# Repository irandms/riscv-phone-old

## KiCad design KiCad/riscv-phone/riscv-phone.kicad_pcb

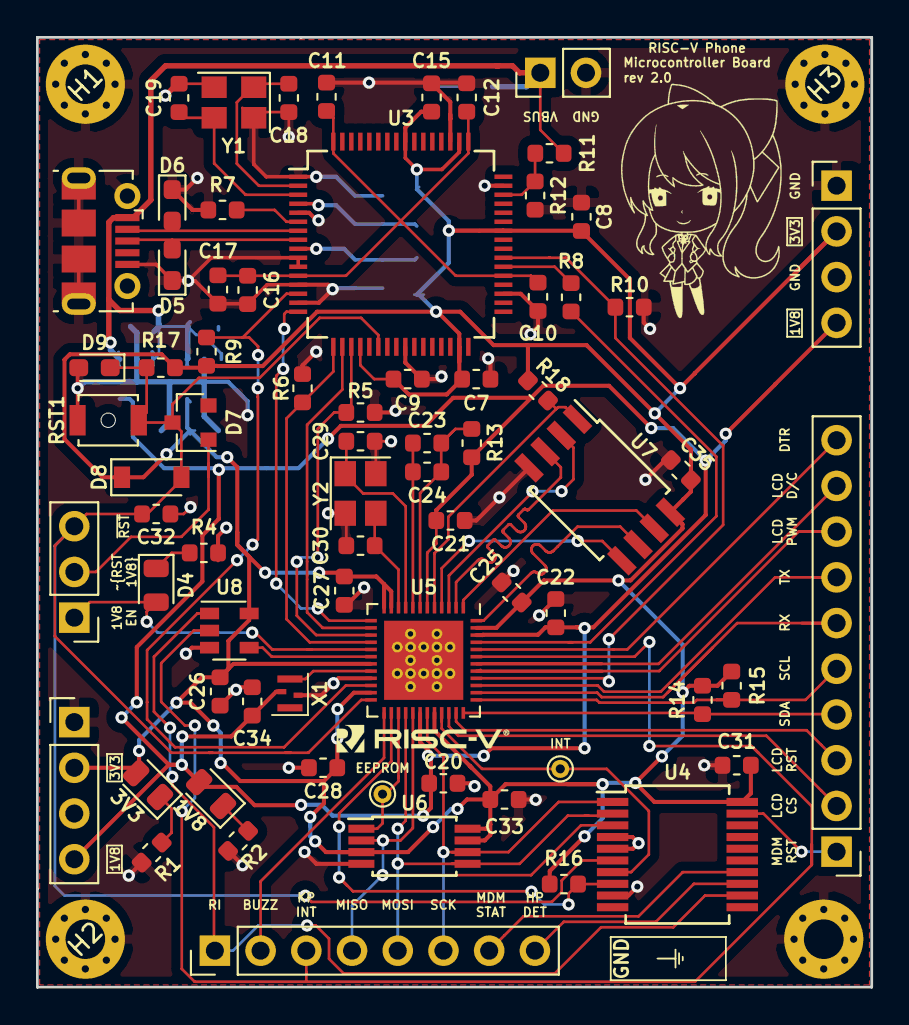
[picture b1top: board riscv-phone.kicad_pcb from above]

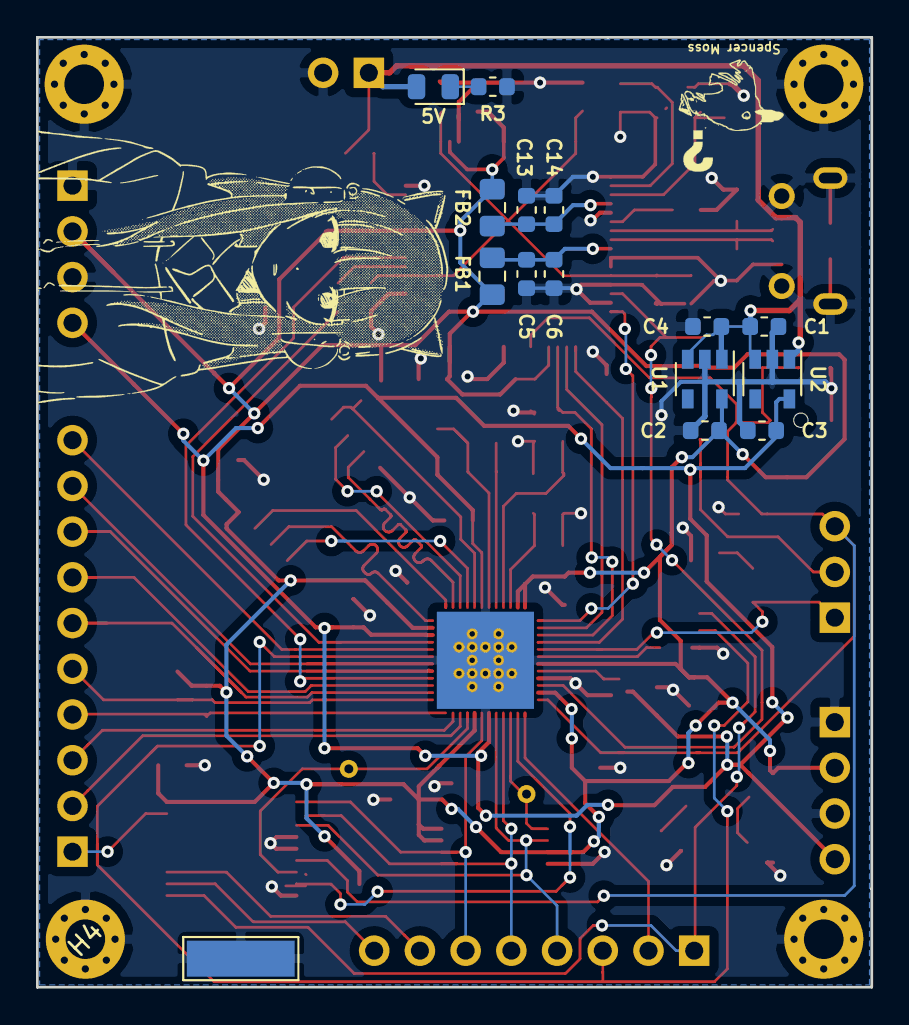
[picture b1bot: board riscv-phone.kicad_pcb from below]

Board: 2 copper layers, 46.4 x 52.8 mm, 90 parts (16 on the bottom side), 61 nets.

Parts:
1V8: 1V8; LED_0805_2012Metric
3V3: 3V3; LED_0805_2012Metric
5V: VBUS_LED; LED_0805_2012Metric
C1, C2, C3, C4, C22, C24, C27: 1uF; C_0603_1608Metric
C5, C13, C16: 4.7uF; C_0603_1608Metric
C6, C7, C8, C9, C10, C11, C12, C14, C15, C17, C20, C21, C23, C25, C26, C28, C31, C33, C34, C35: 0.1uF; C_0603_1608Metric
C18, C19, C29, C30: 12pF; C_0603_1608Metric
C32: 10nF; C_0603_1608Metric
D4: 1V8; LED_0805_2012Metric
D5, D6, D9: D_TVS; LED_0603_1608Metric_Pad1.05x0.95mm_HandSolder
D7: BAT54L; SOT-23
D8: 1N4448W; D_SOD-123
EEPROM: EEPROM; TestPoint_THTPad_D1.0mm_Drill0.5mm
FB1, FB2: 600R; L_0805_2012Metric_Pad1.15x1.40mm_HandSolder
GND: TestPoint; TestPoint_Pad_2.0x2.0mm
H1, H2, H3, H4: MountingHole_Pad; MountingHole_2.2mm_M2_Pad_Via
INT: INT; TestPoint_THTPad_D1.0mm_Drill0.5mm
J1: Conn_01x02; PinHeader_1x02_P2.54mm_Vertical
J2: USB_B_Micro; USB_Micro-B_Molex-105017-0001
J3, J4: Conn_01x04; PinHeader_1x04_P2.54mm_Vertical
J5: Conn_01x08; PinHeader_1x08_P2.54mm_Vertical
J6: Conn_01x03; PinHeader_1x03_P2.54mm_Vertical
J7: Conn_01x10; PinHeader_1x10_P2.54mm_Vertical
R1, R2, R3, R4: 470; R_0603_1608Metric
R5, R6, R8, R10: 1k; R_0603_1608Metric
R7, R12: 12k; R_0603_1608Metric
R9, R11, R14, R15, R16: 4.7k; R_0603_1608Metric
R13: 100; R_0603_1608Metric
R17, R18: 100k; R_0603_1608Metric
RST1: Reset; SW_SPST_B3U-1000P-B
U1: TLV75533PDBV; SOT-23-5
U2: TLV75518PDBV; SOT-23-5
U3: FT2232H; LQFP-64_10x10mm_P0.5mm
U4: MCP23S08_SS; SSOP-20_5.3x7.2mm_P0.65mm
U5: FE310-G002; QFN-48-1EP_6x6mm_P0.4mm_EP4.66x4.66mm_ThermalVias
U6: M95256-WDW6P; TSSOP-8_4.4x3mm_P0.65mm
U7: IL25LP128; SOIJ-8_5.3x5.3mm_P1.27mm
U8: 74AHC1G08; SOT-23-5
X1: SiT1533; Crystal_SMD_2012-4Pin_2.0x1.2mm
Y1: 12 MHz; Crystal_SMD_3225-4Pin_3.2x2.5mm
Y2: 16 MHz; Crystal_SMD_3225-4Pin_3.2x2.5mm

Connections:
+1V8: 1V8.2, C3.1, C20.1, C21.1, C22.1, C34.1, J3.4, J4.4, R13.1, U2.5, U5.6, U5.30, U5.46, X1.4
+3V3: 3V3.2, C2.1, C7.1, C8.1, C9.1, C15.1, C25.1, C26.1, C27.1, C28.1, C31.1, C33.1, C35.1, D8.1, FB1.2, FB2.2, J3.2, J4.2, R9.1, R14.1, R15.1, R16.1, R17.1, R18.1, U1.5, U3.20, U3.31, U3.42, U3.50, U3.56, U4.20, U5.11, U5.12, U5.19, U5.23, U5.32, U5.47, U6.3, U6.7, U6.8, U7.8, U8.5
/Microcontroller/1V8_EN: D4.2, J6.1, U5.17
/Microcontroller/BUZZER: J5.2, U5.25
/Microcontroller/DBG_TO_MCU: R8.1, U5.45
/Microcontroller/DTR: J7.10, U5.44
/Microcontroller/EEPROM_CS: EEPROM.1, U5.27, U6.1
/Microcontroller/FT_RESET: R9.2, U3.14, U5.22
/Microcontroller/HP_DET_INT: J5.8, U4.13
/Microcontroller/INT_CTRL_CS: INT.1, U4.7, U5.33
/Microcontroller/INT_CTRL_INT: R16.2, U4.8, U5.26
/Microcontroller/IO0: U5.4, U7.5
/Microcontroller/IO1: U5.3, U7.2
/Microcontroller/IO2: U5.2, U7.3
/Microcontroller/IO3: U5.1, U7.7
/Microcontroller/JTAG_SRST: C32.1, D7.3, D8.2, D9.1, J6.3, R17.2, RST1.2, U3.22, U4.6, U5.24
/Microcontroller/JTAG_TCK: U3.16, U5.13
/Microcontroller/JTAG_TDI: R6.1, U3.17, U5.16
/Microcontroller/JTAG_TDO: U3.18, U5.14
/Microcontroller/JTAG_TMS: R5.1, U3.19, U5.15
/Microcontroller/KEYPAD_INT: J5.3, U5.43, U8.2
/Microcontroller/LCD_CS: J7.2, U5.34
/Microcontroller/LCD_DC: J7.9, U5.42
/Microcontroller/LCD_LED_PWM: J7.8, U5.41
/Microcontroller/LCD_RST: J7.3, U5.35
/Microcontroller/LFALTCLK: U5.20, X1.3
/Microcontroller/MCU_TO_MODEM: J7.7, U5.39
/Microcontroller/MISO: J5.4, U4.3, U5.29, U6.2
/Microcontroller/MODEM_RST: J7.1, U4.19
/Microcontroller/MODEM_STATUS: J5.7, U4.14
/Microcontroller/MODEM_TO_MCU: J7.6, U5.38
/Microcontroller/MOSI: J5.5, U4.2, U5.28, U6.5
/Microcontroller/PLL_AVDD: C23.1, C24.1, R13.2, U5.7
/Microcontroller/PLL_AVSS: C23.2, C24.2, U5.8
/Microcontroller/QSPI_CS: R18.2, U5.5, U7.1
/Microcontroller/QSPI_SCK: U5.48, U7.6
/Microcontroller/RESET_N_1V8: D7.1, J6.2
/Microcontroller/RI_INT: J5.1, U4.12, U8.1
/Microcontroller/SCK: J5.6, U4.1, U5.31, U6.6
/Microcontroller/SCL: J7.5, R15.2, U5.37
/Microcontroller/SDA: J7.4, R14.2, U5.36
/Microcontroller/WAKEUP_N: U5.18, U8.4
/Program and Debug/FT_RX: R10.1, U3.39, U5.40
/Program and Debug/FT_UART_TX: R8.2, U3.38
/Program and Debug/USB_D+: D5.2, J2.3, U3.8
/Program and Debug/USB_D-: D6.2, J2.2, U3.7
/Program and Debug/VCORE_FT: C10.1, C11.1, C12.1, C16.1, C17.1, U3.12, U3.37, U3.49, U3.64
/Program and Debug/VPHY_FT: C13.1, C14.1, FB2.1, U3.4
/Program and Debug/VPLL_FT: C5.1, C6.1, FB1.1, U3.9
/Program and Debug/VUSB: 5V.2, C1.1, C4.1, J1.1, J2.1, R11.1, U1.1, U1.3, U2.1, U2.3
GND: C1.2, C2.2, C3.2, C4.2, C5.2, C6.2, C7.2, C8.2, C9.2, C10.2, C11.2, C12.2, C13.2, C14.2, C15.2, C16.2, C17.2, C18.2, C19.2, C20.2, C21.2, C22.2, C25.2, C26.2, C27.2, C28.2, C29.1, C30.2, C31.2, C32.2, C33.2, C34.2, C35.2, D5.1, D6.1, D9.2, GND.1, H1.1, H2.1, H3.1, H4.1, J1.2, J2.5, J2.6, J3.1, J3.3, J4.1, J4.3, R1.2, R2.2, R3.2, R4.2, R5.2, R6.2, R7.2, R10.2, R12.2, RST1.1, U1.2, U2.2, U3.1, U3.5, U3.10, U3.11, U3.13, U3.15, U3.25, U3.35, U3.47, U3.51, U4.4, U4.5, U4.9, U5.21, U5.49, U6.4, U7.4, U8.3, X1.2, Y1.2, Y1.4, Y2.2, Y2.4
unnamed: C18.1, U3.2, Y1.1
unnamed: C19.1, U3.3, Y1.3
unnamed: C29.2, U5.9, Y2.1
unnamed: C30.1, U5.10, Y2.3
unnamed: 3V3.1, R1.1
unnamed: 1V8.1, R2.1
unnamed: 5V.1, R3.1
unnamed: D4.1, R4.1
unnamed: R7.1, U3.6
unnamed: R11.2, R12.1, U3.46

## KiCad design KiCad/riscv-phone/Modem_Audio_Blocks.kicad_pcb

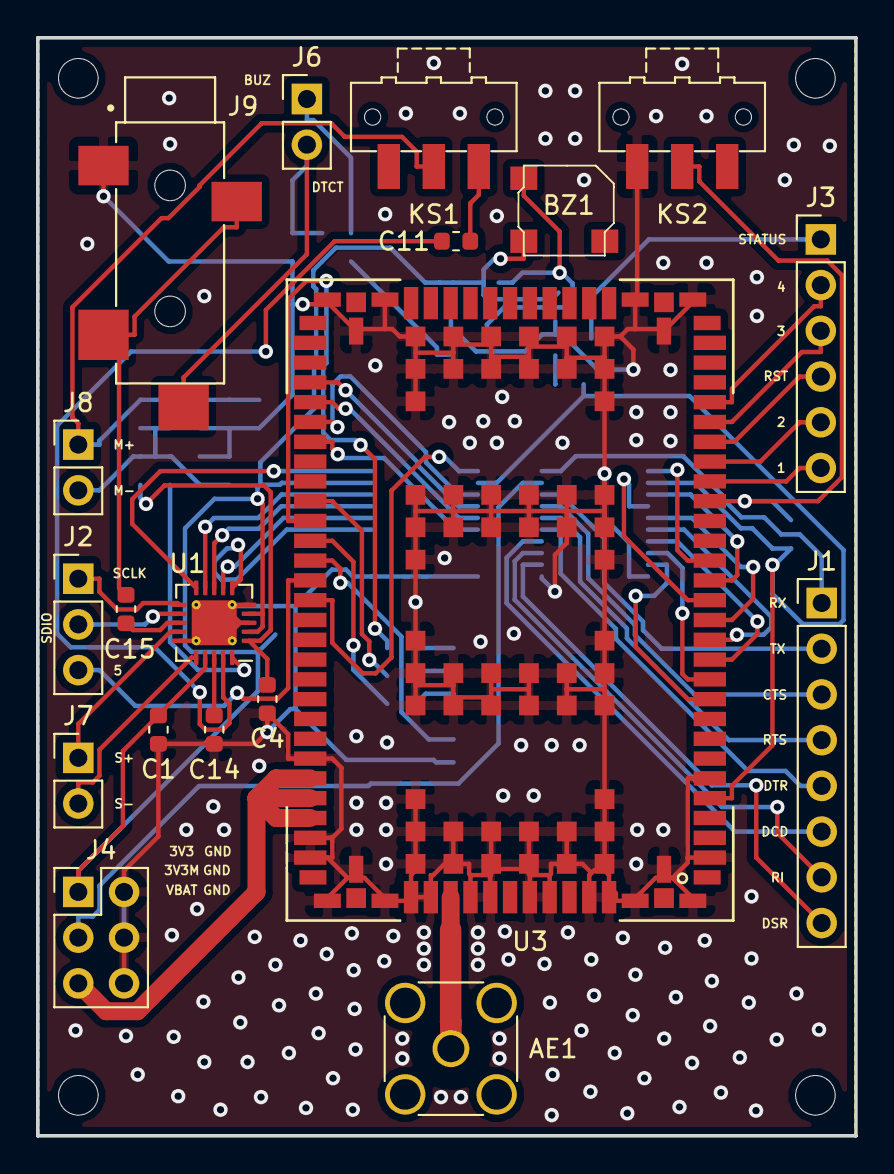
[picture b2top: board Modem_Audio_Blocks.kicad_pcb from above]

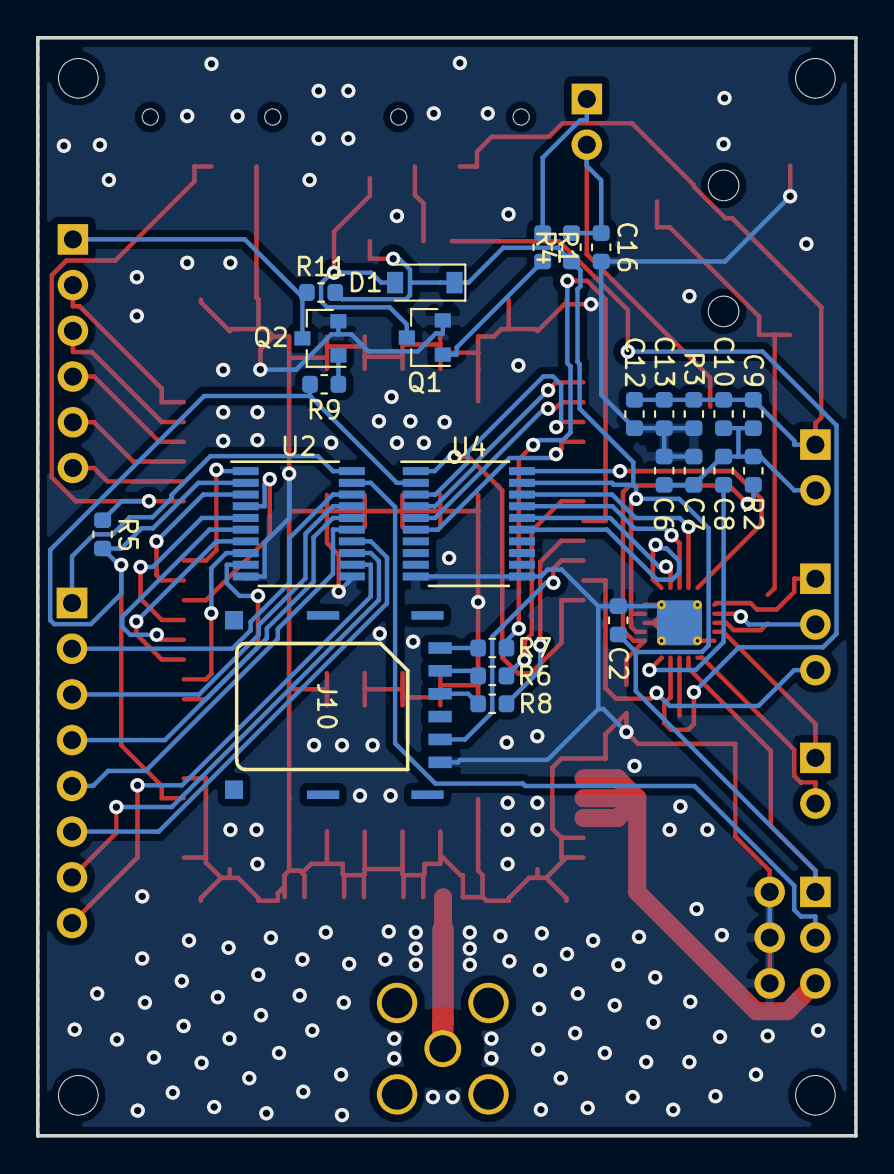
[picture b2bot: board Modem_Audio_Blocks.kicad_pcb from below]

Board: 2 copper layers, 45.4 x 61.0 mm, 48 parts (25 on the bottom side), 65 nets.

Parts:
AE1: Antenna; SMA_Amphenol_132134_Vertical
BZ1: Buzzer; SMT-0540-T-2-R
C1, C2, C4, C14: 4.7uF; C_0603_1608Metric
C6, C9, C12: 10pF; C_0603_1608Metric
C7, C10, C13, C16: 33pF; C_0603_1608Metric
C8, C11, C15: 1uF; C_0603_1608Metric
D1: 1N4448W; D_SOD-123
J1: Conn_01x08; PinHeader_1x08_P2.54mm_Vertical
J2: Conn_01x03; PinHeader_1x03_P2.54mm_Vertical
J3: Conn_01x06; PinHeader_1x06_P2.54mm_Vertical
J4: Conn_02x03_Odd_Even; PinHeader_2x03_P2.54mm_Vertical
J6, J7, J8: Conn_01x02; PinHeader_1x02_P2.54mm_Vertical
J9: SJ-3524-SMT; CUI_SJ-3524-SMT
J10: SIM_Card; Nano SIM Card
KS1: Mic Killswitch; SW_SPDT_CK-JS102011SAQN
KS2: Modem Killswitch; SW_SPDT_CK-JS102011SAQN
Q1, Q2: MMBT3904; SOT-23
R1: 4.7k; R_0603_1608Metric
R2, R3: 1.2k; R_0603_1608Metric
R4, R5: 100k; R_0603_1608Metric
R6, R7, R8: 22; R_0603_1608Metric
R9, R11: 1k; R_0603_1608Metric
U1: NAU8810; QFN-20-1EP_4x4mm_P0.5mm_EP2.5x2.5mm_ThermalVias
U2, U4: TXS0108EPW; TSSOP-20_4.4x6.5mm_P0.65mm
U3: uBlox_TOBY-R200
m1, m2, m3, m4: MountingHole_2.2mm_M2_ISO7380

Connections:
+3V3: BZ1.1, C1.1, C2.1, D1.1, J4.1, R4.1, R11.2, U1.2, U1.4, U1.17, U4.19
/AudioINDIV/ADCOUT: U1.6, U4.15
/AudioINDIV/BCLK: U1.9, U4.18
/AudioINDIV/BUZZER: J6.1, R1.2
/AudioINDIV/DACIN: U1.7, U4.16
/AudioINDIV/FS: U1.8, U4.17
/AudioINDIV/HEADPHONE_DETECT: C16.1, J6.2, J9.4, R4.2
/AudioINDIV/MCLK: U1.10, U4.20
/AudioINDIV/MIC+: C8.1, U1.20
/AudioINDIV/MIC-: C11.1, U1.19
/AudioINDIV/SCLK: J2.1, U1.11
/AudioINDIV/SDIO: J2.2, U1.12
/AudioINDIV/SPK+: J7.1, U1.14
/AudioINDIV/SPK-: J7.2, U1.16
/AudioINDIV/oMIC+: C6.2, C7.2, C8.2, C9.1, C10.1, J8.2, R2.1
/AudioINDIV/oMIC-: C9.2, C10.2, C12.1, C13.1, J8.1, KS1.2, R3.2
/GPIO5: J2.3, U3.60
/ModemINDIV/CTS: J1.3, U2.17
/ModemINDIV/DCD: J1.6, U2.14
/ModemINDIV/DSR: J1.8, U2.12
/ModemINDIV/DTR: J1.5, U2.15
/ModemINDIV/GPIO1: J3.6, U3.21
/ModemINDIV/GPIO2: J3.5, U3.22
/ModemINDIV/GPIO3: J3.3, U3.24
/ModemINDIV/GPIO4: J3.2, U3.25
/ModemINDIV/GPIO6: U3.61, U4.1
/ModemINDIV/MODEM_RX: J1.1, U2.20
/ModemINDIV/MODEM_TX: J1.2, U2.18
/ModemINDIV/RESET_N_1V8: J3.4, U3.23
/ModemINDIV/RI: J1.7, U2.13
/ModemINDIV/RTS: J1.4, U2.16
/ModemINDIV/STATUS: J3.1, Q2.3, R11.1
/ModemINDIV/VBAT: J4.5, U3.70, U3.71, U3.72
/ModemINDIV/VDD_1V8: R5.1, R9.2, U2.2, U3.5, U4.2
/ModemINDIV/VDD_3V3_MOFF: J4.3, U2.19
GND: C1.2, C2.2, C4.2, C6.1, C7.1, C12.2, C13.2, C14.2, C16.2, J4.2, J4.4, J4.6, J9.1, J10.5, KS2.3, Q1.2, Q2.2, R3.1, U1.3, U1.5, U1.15, U1.21, U2.10, U2.11, U3.2, U3.6, U3.30, U3.32, U3.44, U3.46, U3.69, U3.73, U3.74, U3.76, U3.78, U3.79, U3.80, U3.82, U3.83, U3.85, U3.86, U3.88, U3.89, U3.90, U3.92, U3.93, U3.94, U3.95, U3.96, U3.97, U3.98, U3.99, U3.100, U3.101, U3.102, U3.103, U3.104, U3.105, U3.106, U3.107, U3.108, U3.109, U3.110, U3.111, U3.112, U3.113, U3.114, U3.115, U3.116, U3.117, U3.118, U3.119, U3.120, U3.121, U3.122, U3.123, U3.124, U3.125, U3.126, U3.127, U3.128, U3.129, U3.130, U3.131, U3.132, U3.133, U3.134, U3.135, U3.136, U3.137, U3.138, U3.139, U3.140, U3.141, U3.142, U3.143, U3.144, U3.145, U3.146, U3.147, U3.148, U3.149, U3.150, U3.151, U3.152, U4.10, U4.11
unnamed: AE1.1, U3.81
unnamed: BZ1.2, D1.2, Q1.3
unnamed: C4.1, R2.2, U1.1
unnamed: C11.2, KS1.1
unnamed: C14.1, U1.18
unnamed: C15.1, J9.2, J9.3
unnamed: C15.2, U1.13
unnamed: J10.1, U3.59
unnamed: J10.2, R8.2
unnamed: J10.3, R6.2
unnamed: J10.7, R7.2
unnamed: KS2.2, R5.2, U3.20
unnamed: Q1.1, R1.1
unnamed: Q2.1, R9.1
unnamed: R6.1, U3.56
unnamed: R7.1, U3.57
unnamed: R8.1, U3.58
unnamed: U2.1, U3.17
unnamed: U2.3, U3.16
unnamed: U2.4, U3.15
unnamed: U2.5, U3.14
unnamed: U2.6, U3.13
unnamed: U2.7, U3.12
unnamed: U2.8, U3.11
unnamed: U2.9, U3.10
unnamed: U3.50, U4.4
unnamed: U3.51, U4.5
unnamed: U3.52, U4.3
unnamed: U3.53, U4.6

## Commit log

2019-01-31 Initial microcontroller board
2019-02-01 Deleted other subschematics, added breakout headers
2019-02-01 Modem and Audio PCB
2019-02-01 Added GND planes and mounting holes
2019-02-01 Added GND vias
2019-02-02 added mounting holes, finalized layout
2019-02-02 Add missing symbol and footprint tables
2019-02-03 GPIO6 to MCLK
2019-02-03 Added Status circuit, GPIO6 to MCLK
2019-02-03 Added heircarchal labels, switched some connector pins
2019-02-03 Final PCB with added changes
2019-02-03 Autorouting rules
2019-02-03 fixed GND plane inside SMT connector
2019-02-04 Finalized schematic and layout for individual block
2019-02-04 Finalized pcb layout
2019-04-14 rev 1.1
2019-04-18 Revision 2.0
2019-07-22 Add Solderpad Hardware Licence Version 2.0
